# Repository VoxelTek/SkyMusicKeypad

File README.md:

# Sky Music Keypad
 
A 5x3 grid of MX switches connected to an RP2040-Zero, intended for playing music in the same style as seen in [Sky: Children Of The Light](https://www.thatskygame.com/).

This project was initially created as a birthday present for a friend, but I realised that the community might appreciate this project, and may be able to improve on it in ways I never could.

This device supports MIDI output, keyboard emulation for [Sky Music Nightly](https://specy.github.io/skyMusic), and keyboard emulation for the PC port of Sky.

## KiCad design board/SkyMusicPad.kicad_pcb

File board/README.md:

# SkyMusicPad

A PCB design for a physical replication of the Sky music pad, from Sky: Children Of The Light. 

It uses mechanical keyboard switches for each note, set-up in a matrix arrangement, hooked up to an RP2040-Zero running CircuitPython. MIDI data is outputted over USB to a computer.

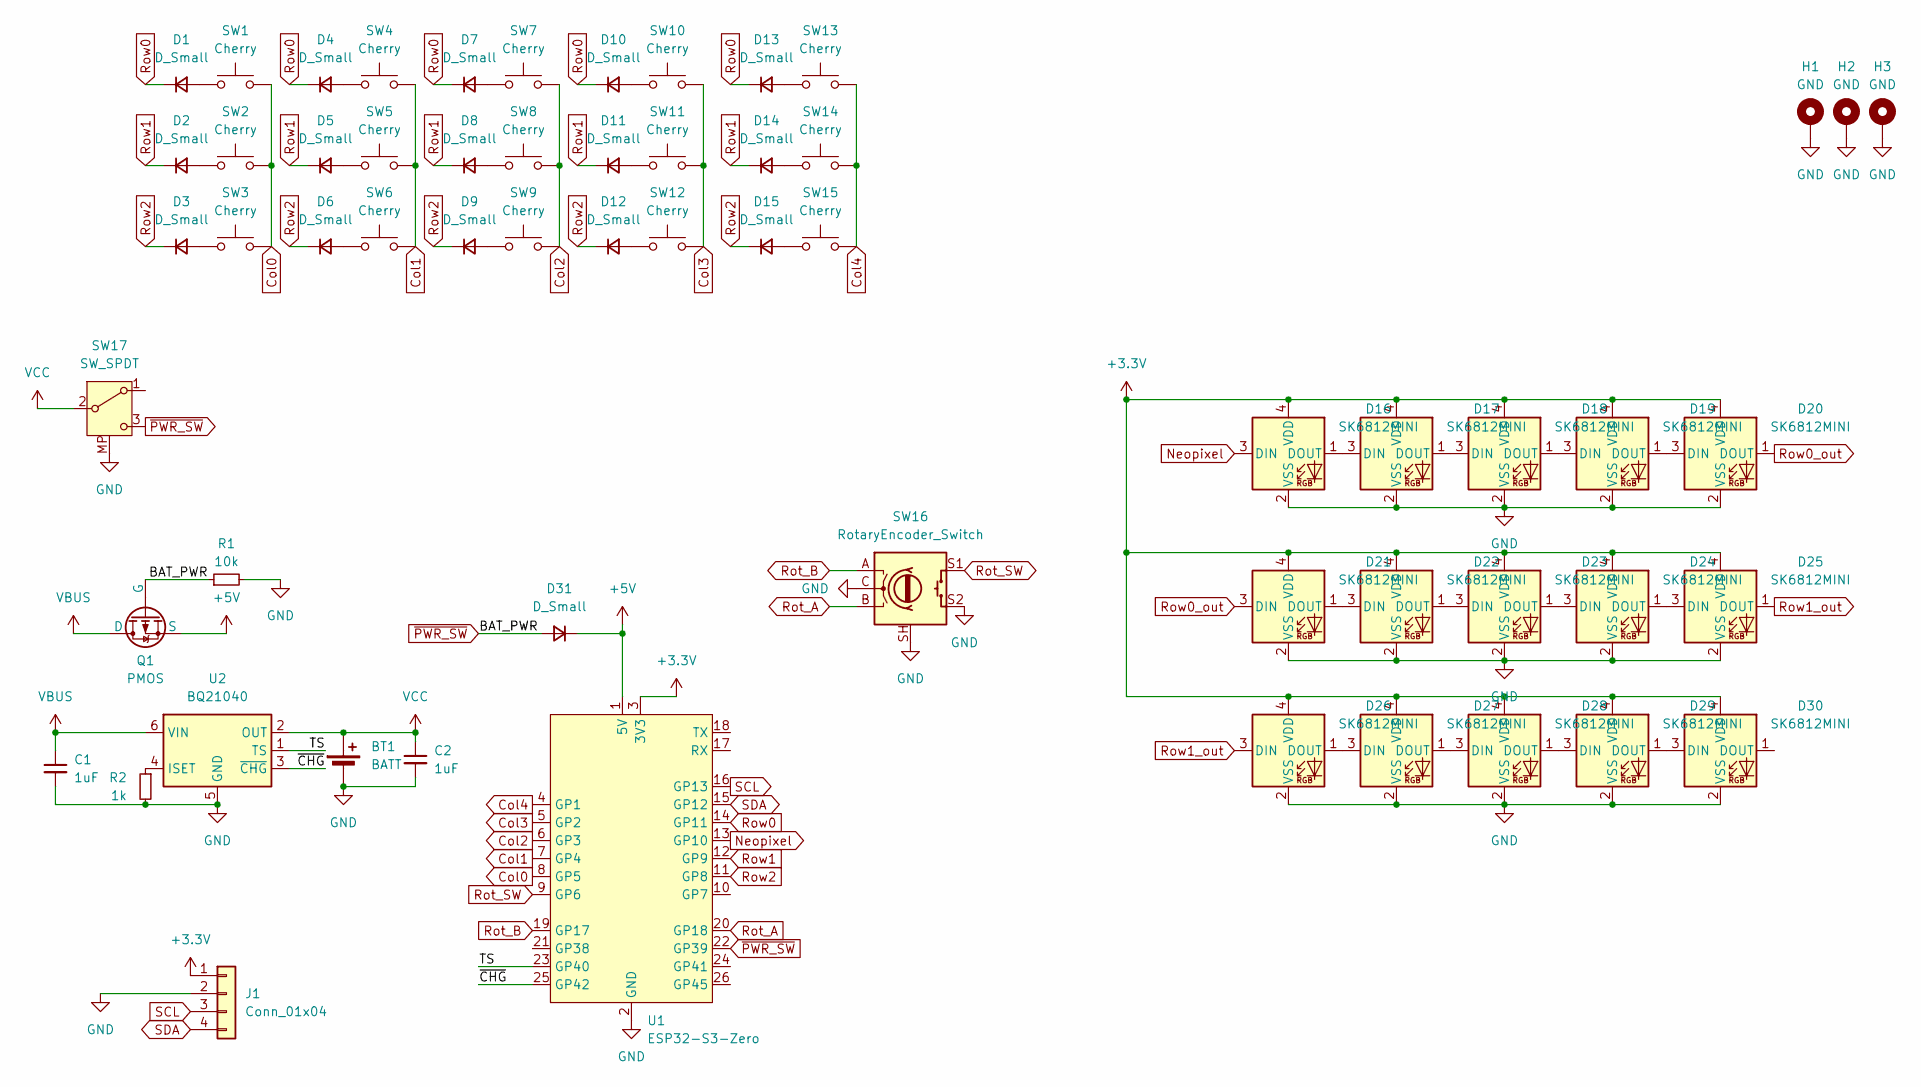
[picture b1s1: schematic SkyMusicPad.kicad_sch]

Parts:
BT1: BATT; JST_PH_B2B-PH-SM4-TB_1x02-1MP_P2.00mm_Vertical
C1, C2: 1uF; C_0402_1005Metric
D1, D2, D3, D4, D5, D6, D7, D8, D9, D10, D11, D12, D13, D14, D15: D_Small; D_MiniMELF_silkMoved
D16, D17, D18, D19, D20, D21, D22, D23, D24, D25, D26, D27, D28, D29, D30: SK6812MINI; LED_SK6812MINI_REVERSE
D31: D_Small; D_SOD-323_HandSoldering
H1, H2, H3: GND; MountingHole_2.2mm_M2_Pad_Via
J1: Conn_01x04; OLED_DFR0648
Q1: PMOS; SOT-23
R1: 10k; R_0402_1005Metric
R2: 1k; R_0402_1005Metric
SW1, SW2, SW3, SW4, SW5, SW6, SW7, SW8, SW9, SW10, SW11, SW12, SW13, SW14, SW15: Cherry; SW_Cherry_MX_1.00u_PCB
SW16: RotaryEncoder_Switch; RotaryEncoder_Bourns_Vertical_PEC12R-3x17F-Sxxxx
SW17: SW_SPDT; SSAJ120100
U1: ESP32-S3-Zero
U2: BQ21040; SOT-23-6

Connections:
+3.3V: D16.4 (VDD), D17.4 (VDD), D18.4 (VDD), D19.4 (VDD), D20.4 (VDD), D21.4 (VDD), D22.4 (VDD), D23.4 (VDD), D24.4 (VDD), D25.4 (VDD), D26.4 (VDD), D27.4 (VDD), D28.4 (VDD), D29.4 (VDD), D30.4 (VDD), J1.1, U1.3 (3V3)
+5V: D31.1 (K), Q1.2 (S), U1.1 (5V)
/TS: U1.23 (GP40), U2.1 (TS)
/~CHG: U1.25 (GP42), U2.3 (~CHG)
Col0: SW1.1, SW2.1, SW3.1, U1.8 (GP5)
Col1: SW4.1, SW5.1, SW6.1, U1.7 (GP4)
Col2: SW7.1, SW8.1, SW9.1, U1.6 (GP3)
Col3: SW10.1, SW11.1, SW12.1, U1.5 (GP2)
Col4: SW13.1, SW14.1, SW15.1, U1.4 (GP1)
GND: BT1.2 (-), BT1.MP, C1.2, C2.2, D16.2 (VSS), D17.2 (VSS), D18.2 (VSS), D19.2 (VSS), D20.2 (VSS), D21.2 (VSS), D22.2 (VSS), D23.2 (VSS), D24.2 (VSS), D25.2 (VSS), D26.2 (VSS), D27.2 (VSS), D28.2 (VSS), D29.2 (VSS), D30.2 (VSS), H1.1, H2.1, H3.1, J1.2, R1.2, R2.2, SW16.C, SW16.S2, SW16.SH (Shell_Ground), SW17.MP, U1.2 (GND), U2.5 (GND)
Neopixel: D16.3 (DIN), U1.13 (GP10)
unnamed: D1.2 (A), SW1.2
unnamed: D2.2 (A), SW2.2
unnamed: D3.2 (A), SW3.2
unnamed: D4.2 (A), SW4.2
unnamed: D5.2 (A), SW5.2
unnamed: D6.2 (A), SW6.2
unnamed: D7.2 (A), SW7.2
unnamed: D8.2 (A), SW8.2
unnamed: D9.2 (A), SW9.2
unnamed: D10.2 (A), SW10.2
unnamed: D11.2 (A), SW11.2
unnamed: D12.2 (A), SW12.2
unnamed: D13.2 (A), SW13.2
unnamed: D14.2 (A), SW14.2
unnamed: D15.2 (A), SW15.2
unnamed: D16.1 (DOUT), D17.3 (DIN)
unnamed: D17.1 (DOUT), D18.3 (DIN)
unnamed: D18.1 (DOUT), D19.3 (DIN)
unnamed: D19.1 (DOUT), D20.3 (DIN)
unnamed: D21.1 (DOUT), D22.3 (DIN)
unnamed: D22.1 (DOUT), D23.3 (DIN)
unnamed: D23.1 (DOUT), D24.3 (DIN)
unnamed: D24.1 (DOUT), D25.3 (DIN)
unnamed: D26.1 (DOUT), D27.3 (DIN)
unnamed: D27.1 (DOUT), D28.3 (DIN)
unnamed: D28.1 (DOUT), D29.3 (DIN)
unnamed: D29.1 (DOUT), D30.3 (DIN)
unnamed: R2.1, U2.4 (ISET)
Rot_A: SW16.B, U1.20 (GP18)
Rot_B: SW16.A, U1.19 (GP17)
Rot_SW: SW16.S1, U1.9 (GP6)
Row0: D1.1 (K), D4.1 (K), D7.1 (K), D10.1 (K), D13.1 (K), U1.14 (GP11)
Row0_out: D20.1 (DOUT), D21.3 (DIN)
Row1: D2.1 (K), D5.1 (K), D8.1 (K), D11.1 (K), D14.1 (K), U1.12 (GP9)
Row1_out: D25.1 (DOUT), D26.3 (DIN)
Row2: D3.1 (K), D6.1 (K), D9.1 (K), D12.1 (K), D15.1 (K), U1.11 (GP8)
SCL: J1.3, U1.16 (GP13)
SDA: J1.4, U1.15 (GP12)
VBUS: C1.1, Q1.3 (D), U2.6 (VIN)
VCC: BT1.1 (+), C2.1, SW17.2 (B), U2.2 (OUT)
~PWR_SW: D31.2 (A), Q1.1 (G), R1.1, SW17.3 (C), U1.22 (GP39)

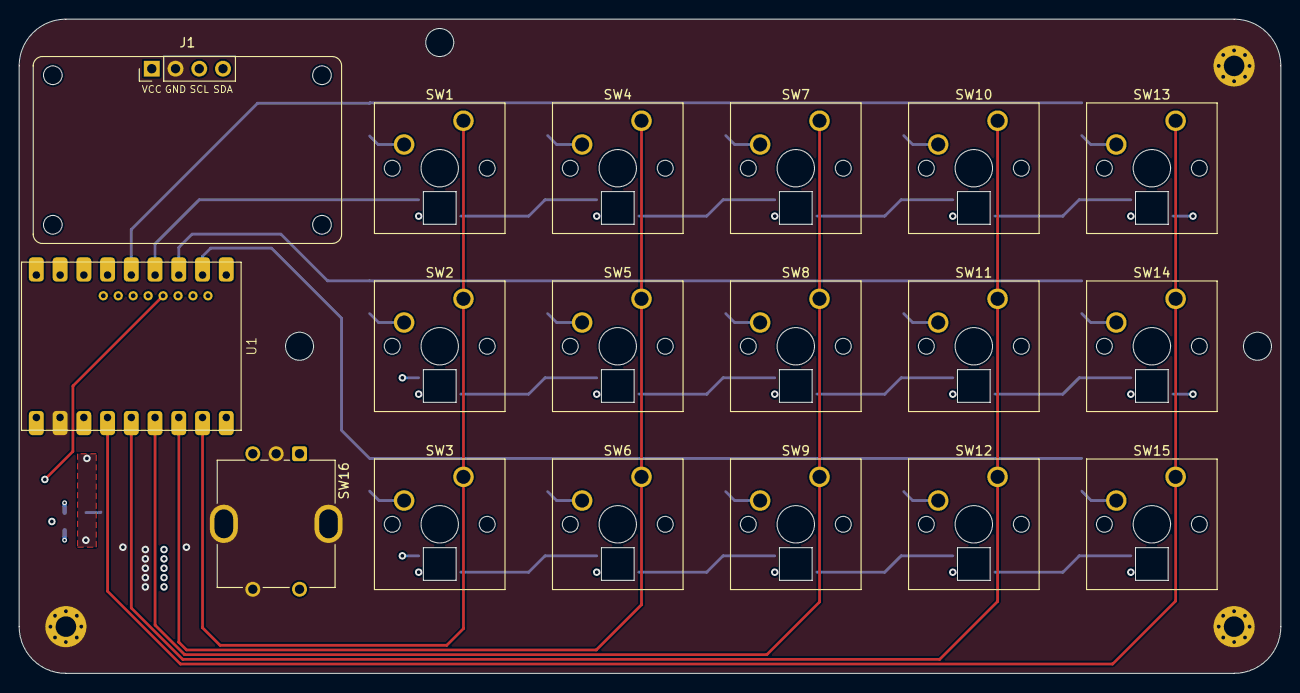
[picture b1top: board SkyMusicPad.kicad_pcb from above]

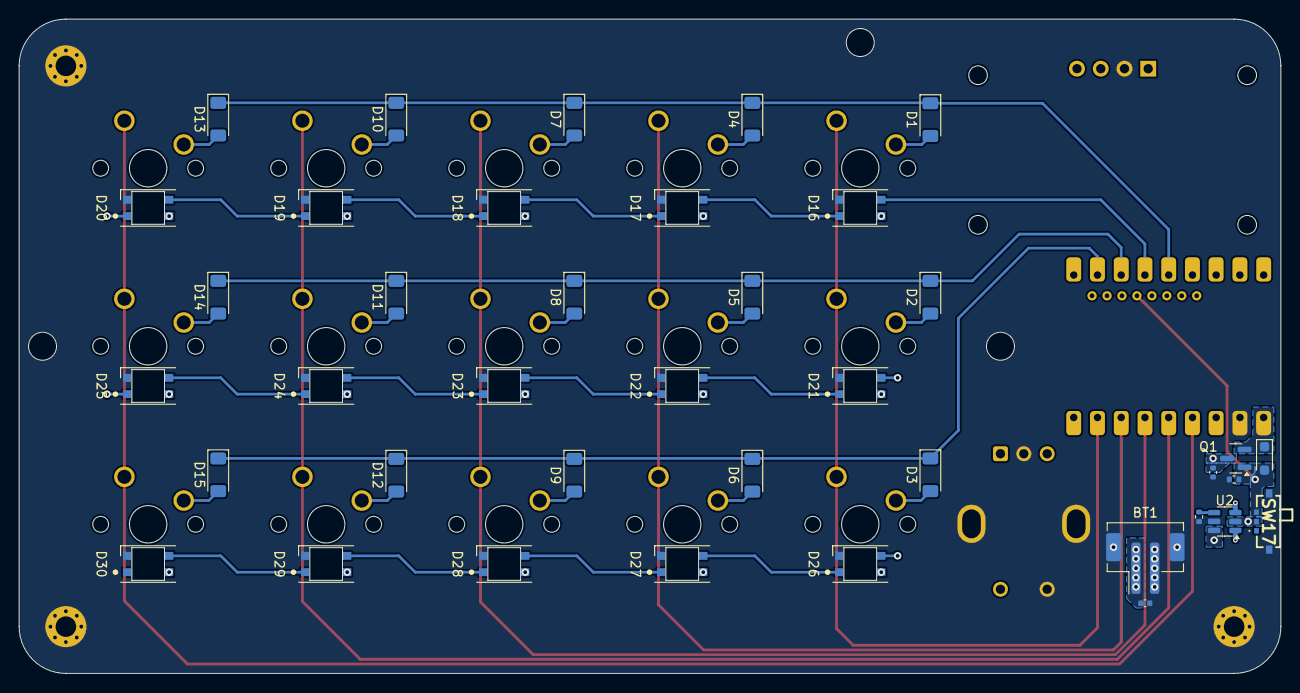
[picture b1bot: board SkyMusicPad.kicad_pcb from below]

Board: 4 copper layers, 135.0 x 70.0 mm, 60 parts (39 on the bottom side), 52 nets.

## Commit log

2023-10-31 Adjusted rotary encoder to have common point GND
2023-10-31 Clean-up of code, add button to reset encoder
2023-11-01 implemented all RGB LEDs
2023-11-01 KiCad backup update, has no relevance.
2023-11-01 Introduce reverse mount library into repo
2023-11-01 Fixed the use of the incorrect footprint for MX
2023-11-16 Updated the code to support keyboard output
    Modified the code so that now it can optionally output a keyboard button signal instead of just MIDI.
2023-12-03 Update README.md
    inclusion of word
2024-01-11 File system cleanup
2024-04-16 misc changes
2024-04-17 Redesign, sorta
2024-04-17 Remove locks etc
2024-04-17 misc
2024-04-17 CURVES!!
2024-04-17 backup update
2024-04-18 Add outline, for use with 3D CAD
2024-04-18 Update README.md
    Rewrote text, added images
2024-04-19 Gerber regeneration
2024-04-23 Update LICENSE
2024-04-23 Create code LICENSE
2024-04-23 Create PCB LICENSE
2024-05-19 Hardware changes, 3D regen
2024-05-20 Fix code for game mode
2024-05-20 Initiating development of companion app
2024-05-20 More misc developments on companion app
2024-05-22 Developing base for config system
2024-05-22 More companion development
2024-05-22 Adjusting design for larger board
2024-05-23 Board and code update
2024-05-23 Misc code edits
2024-05-28 More misc updates
2024-06-02 Gerber regen, misc changes
2024-06-03 Update libraries, complete JSON import
2024-06-03 JSON serial transmission functional
2024-06-04 Extremely close to completion!
2024-06-04 Misc changes, beginning compilation
2024-06-04 Major changes to code, improved functionality
2024-06-05 Port to PySide, begin rotary encoder
2024-06-05 Fixing up MIDI display mode
2024-06-05 Reset UI layout
2024-06-05 Begin development of dock for advanced options
2024-06-06 More misc changes
2024-07-14 Change global net shapes, move encoder position
2024-07-14 Backup updates
2024-07-15 More code work, finishing touches and cleanup
2024-07-15 Failing in trying to add advanced options
2024-08-28 Add submodule, begin ESP32-S3-Zero development
2024-08-28 Code migration
    - Remove CircuitPython code
    - Begin Arduino code development
    - Add patched BLE Keyboard library
2024-08-28 Fix submodule, remove PCB lock
2024-08-28 Fix code to match relocated submodule
2024-08-28 misc code updates
2024-08-29 Code and PCB updates
2024-08-29 Update ESP32-BLE-Keyboard
2024-08-29 Remove ESP32-BLE-Keyboard submodule
    Currently in the process of fixing up submodules.
2024-08-29 Fix submodules...finally.
2024-08-29 I hate C++. With a burning passion.
2024-09-02 Further board and code development.
2024-09-02 Remove locks
2024-09-03 I hate C still
2024-09-03 Fix and add LEDs
2024-09-03 Backport schematic and PCB
2024-09-03 i hate this
2024-09-03 Transfer code stuff
2024-09-04 Fix 3D model for LEDs
2024-09-04 Fix minor issues, adjust diode silkscreen
2024-09-06 Adjusted LED silk, need to fix encoder
2024-09-20 misc updates
2025-02-13 upload changes
2025-02-13 Components placed
2025-02-13 Slight placement adjustments
2025-02-13 Add charging circuit, finalising design
2025-02-13 Update ESP32-S3-Zero_KiCad
2025-02-13 Begin work on battery
2025-02-14 Near completion, pretty much done I think
2025-02-14 Change board colours
2025-02-16 more misc changes and improvements
2025-05-21 Redo charging circuit
2025-05-21 AAAAAAAAAAAAAAAAAAAAAAA
